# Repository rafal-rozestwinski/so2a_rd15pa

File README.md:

# so2a_rd15pa

Go to the [FULL BOARD](v1/so2a_rd15_pa_v1/) or [MINIMAL BOARD](v1/so2a_rd15_pa_v1-minimal/)

## Images

## Join HamBrewers on Telegram:

http://t.me/hambrewers

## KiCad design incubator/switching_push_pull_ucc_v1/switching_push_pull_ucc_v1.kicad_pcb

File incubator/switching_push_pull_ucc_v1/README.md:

# switching_push_pull_amp

## Join HamBrewers on Telegram:

http://t.me/hambrewers

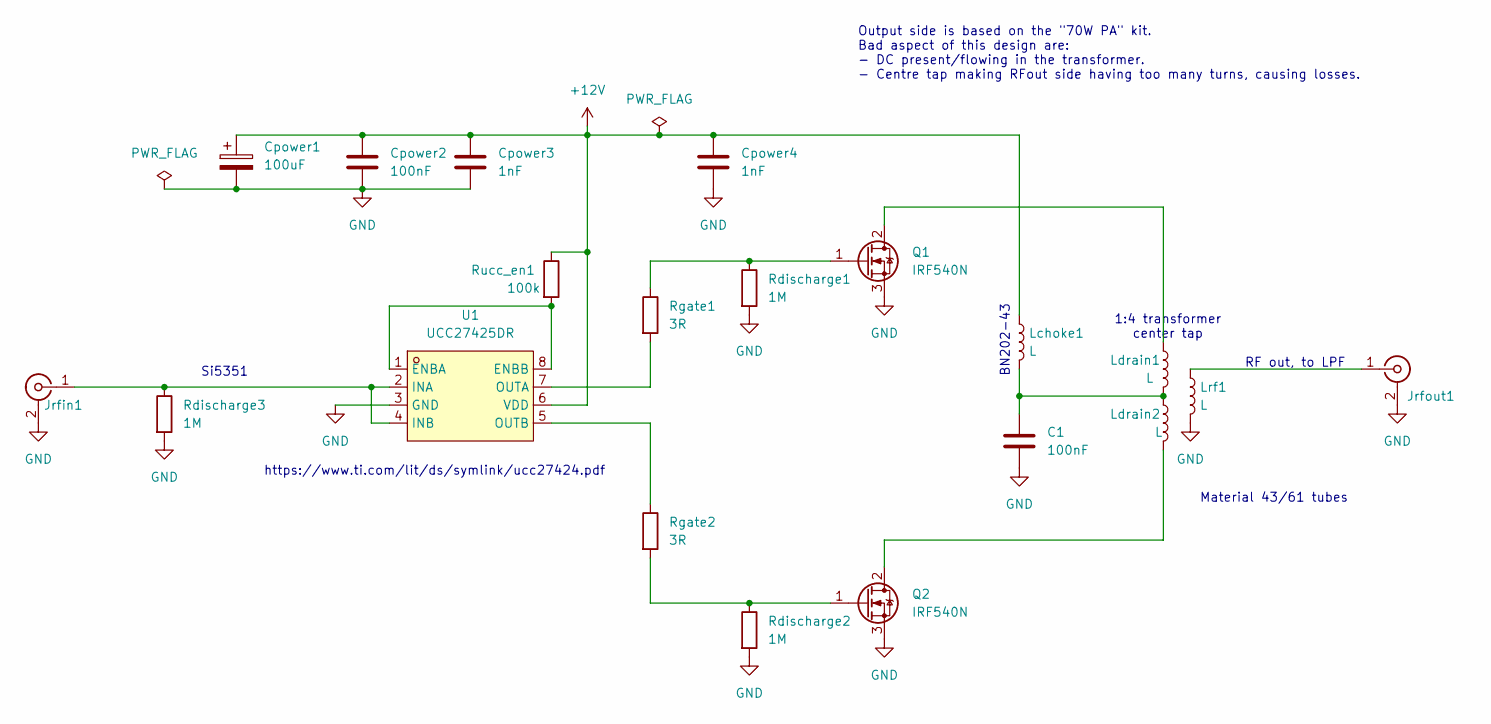
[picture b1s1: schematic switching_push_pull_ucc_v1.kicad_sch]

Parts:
C1: 100nF; C_1206_3216Metric
Cpower1: 100uF; C_Elec_8x10.2
Cpower2: 100nF; C_1206_3216Metric
Cpower3, Cpower4: 1nF; C_1206_3216Metric
Jrfin1: Conn_Coaxial; SMA_EDGELAUNCH_Modded
Jrfout1: Conn_Coaxial; SMA_EDGELAUNCH_Modded
Lchoke1: L; L_Wuerth_HCM-1050
Ldrain1, Ldrain2: L; L_Wuerth_HCM-1050
Lrf1: L; L_Wuerth_HCM-1050
Q1, Q2: IRF540N; TO-220-3_Vertical
Rdischarge1, Rdischarge2, Rdischarge3: 1M; R_0805_2012Metric
Rgate1, Rgate2: 3R; R_2010_5025Metric
Rucc_en1: 100k; R_0805_2012Metric
U1: UCC27425DR; SOIC-8_L4.9-W3.9-P1.27-LS6.0-BL; LCSC Part C1848352

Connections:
+12V: Cpower1.1, Cpower2.1, Cpower3.1, Cpower4.1, Lchoke1.1, Rucc_en1.1, U1.6 (VDD); also elsewhere on the board
GND: C1.2, Cpower1.2, Cpower2.2, Cpower3.2, Cpower4.2, Jrfin1.2 (Ext), Jrfout1.2 (Ext), Lrf1.2, Q1.3 (S), Q2.3 (S), Rdischarge1.2, Rdischarge2.2, Rdischarge3.2, U1.3 (GND)
unnamed: C1.1, Lchoke1.2, Ldrain1.2, Ldrain2.1
unnamed: Jrfin1.1 (In), Rdischarge3.1, U1.2 (INA), U1.4 (INB)
unnamed: Jrfout1.1 (In), Lrf1.1
unnamed: Ldrain1.1, Q1.2 (D)
unnamed: Q1.1 (G), Rdischarge1.1, Rgate1.1
unnamed: Ldrain2.2, Q2.2 (D)
unnamed: Q2.1 (G), Rdischarge2.1, Rgate2.2
unnamed: Rucc_en1.2, U1.1 (ENBA), U1.8 (ENBB)
unnamed: Rgate1.2, U1.7 (OUTA)
unnamed: Rgate2.1, U1.5 (OUTB)

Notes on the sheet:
1:4 transformer center tap
BN202-43
Material 43/61 tubes
https://www.ti.com/lit/ds/symlink/ucc27424.pdf
Output side is based on the "70W PA" kit. Bad aspect of this design are: - DC present/flowing in the transformer. - Centre tap making RFout side having too many turns, causing losses.
Si5351
RF out, to LPF

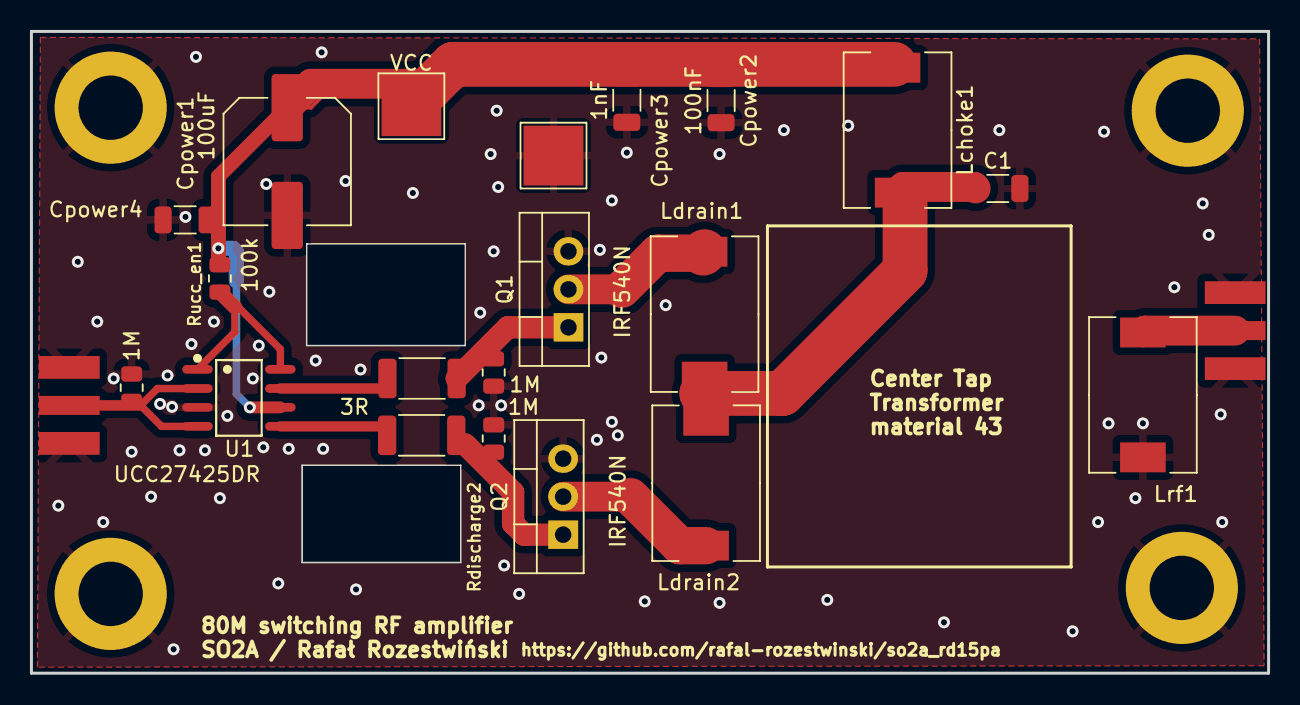
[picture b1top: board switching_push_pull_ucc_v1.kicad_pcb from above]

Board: 2 copper layers, 82.7 x 42.9 mm, 21 parts (0 on the bottom side), 12 nets.

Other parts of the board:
VCC: TestPoint_Pad_4.0x4.0mm

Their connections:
+12V: VCC.1; also elsewhere on the board

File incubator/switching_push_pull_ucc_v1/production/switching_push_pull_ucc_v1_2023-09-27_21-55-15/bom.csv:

Designator,Footprint,Quantity,Value,LCSC Part #
"C1, Cpower2",1206,2,100nF,
Cpower1,C_Elec_8x10.2,1,100uF,
"Cpower3, Cpower4",1206,2,1nF,
"Jrfin1, Jrfout1",SMA_EDGELAUNCH_Modded,2,Conn_Coaxial,
"Lchoke1, Ldrain1, Ldrain2, Lrf1",L_Wuerth_HCM-1050,4,L,
"Q1, Q2",TO-220-3_Vertical,2,IRF540N,
"Rdischarge1, Rdischarge2, Rdischarge3",0805,3,1M,
"Rgate1, Rgate2",2010,2,3R,
Rucc_en1,0805,1,100k,
U1,SOIC-8_L4.9-W3.9-P1.27-LS6.0-BL,1,UCC27425DR,C1848352

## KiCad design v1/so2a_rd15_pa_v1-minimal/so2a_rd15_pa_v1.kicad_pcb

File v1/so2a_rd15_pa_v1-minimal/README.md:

# so2a_rd15pa - MINIMAL

## Join HamBrewers on Telegram:

http://t.me/hambrewers

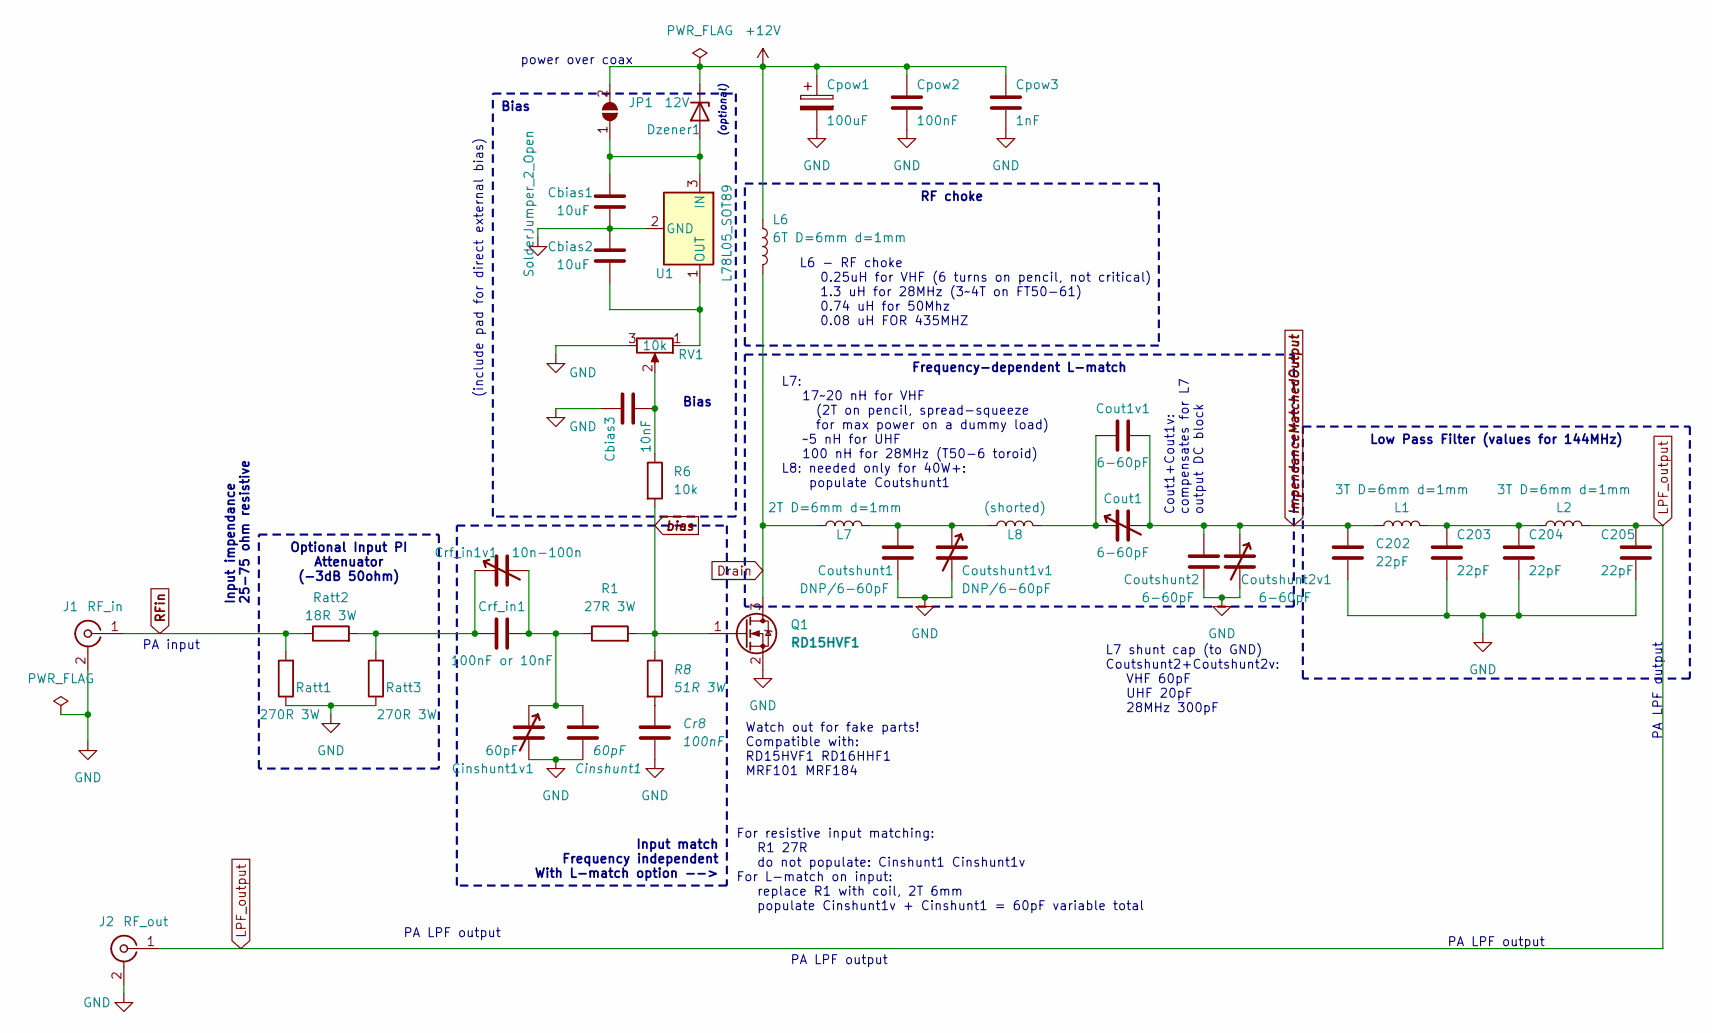
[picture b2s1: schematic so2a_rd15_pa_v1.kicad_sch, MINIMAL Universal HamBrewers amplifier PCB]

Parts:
C202, C203, C204, C205: 22pF; C_1206_3216Metric
Cbias1, Cbias2: 10uF; C_1206_3216Metric
Cbias3: 10nF; C_1206_3216Metric
Cinshunt1: 60pF; C_1206_3216Metric
Cinshunt1v1: 60pF; C_Trimmer_Murata_TZB4-B
Cout1: 6-60pF; C_Trimmer_Murata_TZB4-B
Cout1v1: 6-60pF; C_1206_3216Metric
Coutshunt1: DNP/6-60pF; C_1206_3216Metric
Coutshunt1v1: DNP/6-60pF; C_Trimmer_Murata_TZB4-B
Coutshunt2: 6-60pF; C_1206_3216Metric
Coutshunt2v1: 6-60pF; C_Trimmer_Murata_TZB4-B
Cpow1: 100uF; C_Elec_8x10.2
Cpow2: 100nF; C_1206_3216Metric
Cpow3: 1nF; C_1206_3216Metric
Cr8: 100nF; C_1206_3216Metric
Crf_in1: 100nF or 10nF; C_1206_3216Metric
Crf_in1v1: 10n-100n; C_Trimmer_Murata_TZB4-B
Dzener1: 12V; D_SOD-123
J1: RF_in; SMA_EDGELAUNCH_Modded
J2: RF_out; SMA_EDGELAUNCH_Modded
JP1: SolderJumper_2_Open; SolderJumper-2_P1.3mm_Open_TrianglePad1.0x1.5mm
L1, L2: 3T D=6mm d=1mm; L_Wuerth_HCM-1050
L6: 6T D=6mm d=1mm; L_Wuerth_HCM-1050
L7: 2T D=6mm d=1mm; L_Wuerth_HCM-1050
L8: (shorted); L_Wuerth_HCM-1050
Q1: RD15HVF1; SO2A_TO-220F-3_Vertical_SMD
R1: 27R 3W; R_2010_5025Metric
R6: 10k; R_0805_2012Metric
R8: 51R 3W; R_2010_5025Metric
RV1: 10k; Potentiometer_Vishay_TS53YL_Vertical
Ratt1, Ratt3: 270R 3W; R_2010_5025Metric
Ratt2: 18R 3W; R_2010_5025Metric
U1: L78L05_SOT89; SOT-89-3

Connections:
+12V: Cpow1.1, Cpow2.1, Cpow3.1, Dzener1.1 (K), JP1.2 (B), L6.1; also elsewhere on the board
Drain: L6.2, L7.1, Q1.3 (D)
GND: C202.1, C203.1, C204.1, C205.1, Cbias1.2, Cbias2.1, Cbias3.1, Cinshunt1.1, Cinshunt1v1.2, Coutshunt1.1, Coutshunt1v1.2, Coutshunt2.1, Coutshunt2v1.2, Cpow1.2, Cpow2.2, Cpow3.2, Cr8.1, J1.2 (Ext), J2.2 (Ext), Q1.2 (S), RV1.3, Ratt1.1, Ratt3.1, U1.2 (GND); also elsewhere on the board
ImpendanceMatchedOutput: C202.2, Cout1.2, Cout1v1.1, Coutshunt2.2, Coutshunt2v1.1, L1.1
LPF_output: C205.2, J2.1 (In), L2.2
unnamed: C203.2, C204.2, L1.2, L2.1
unnamed: Cbias3.2, R6.1, RV1.2
unnamed: Cinshunt1.2, Cinshunt1v1.1, Crf_in1.2, Crf_in1v1.2, R1.1
unnamed: Cout1.1, Cout1v1.2, L8.2
unnamed: Coutshunt1.2, Coutshunt1v1.1, L7.2, L8.1
unnamed: Cr8.2, R8.2
unnamed: Crf_in1.1, Crf_in1v1.1, Ratt2.2, Ratt3.2
unnamed: Cbias1.1, Dzener1.2 (A), JP1.1 (A), U1.3 (IN)
unnamed: Cbias2.2, RV1.1, U1.1 (OUT)
RFin: J1.1 (In), Ratt1.2, Ratt2.1
bias: Q1.1 (G), R1.2, R6.2, R8.1

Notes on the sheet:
Frequency-dependent L-match
Bias
Low Pass Filter (values for 144MHz)
Input match Frequency independent With L-match option -->
Optional Input PI Attenuator (-3dB 50ohm)
RF choke
Watch out for fake parts! Compatible with: RD15HVF1 RD16HHF1 MRF101 MRF184
Input impendance 25-75 ohm resistive
PA LPF output
For resistive input matching: R1 27R do not populate: Cinshunt1 Cinshunt1v For L-match on input: replace R1 with coil, 2T 6mm populate Cinshunt1v + Cinshunt1 = 60pF variable total
PA input
L6 - RF choke 0.25uH for VHF (6 turns on pencil, not critical) 1.3 uH for 28MHz (3~4T on FT50-61) 0.74 uH for 50Mhz 0.08 uH FOR 435MHZ
(include pad for direct external bias)
Cout1+Cout1v: compensates for L7 output DC block
power over coax
L7 shunt cap (to GND) Coutshunt2+Coutshunt2v: VHF 60pF UHF 20pF 28MHz 300pF
(optional)
L7: 17~20 nH for VHF (2T on pencil, spread-squeeze for max power on a dummy load) ~5 nH for UHF 100 nH for 28MHz (T50-6 toroid) L8: needed only for 40W+: populate Coutshunt1

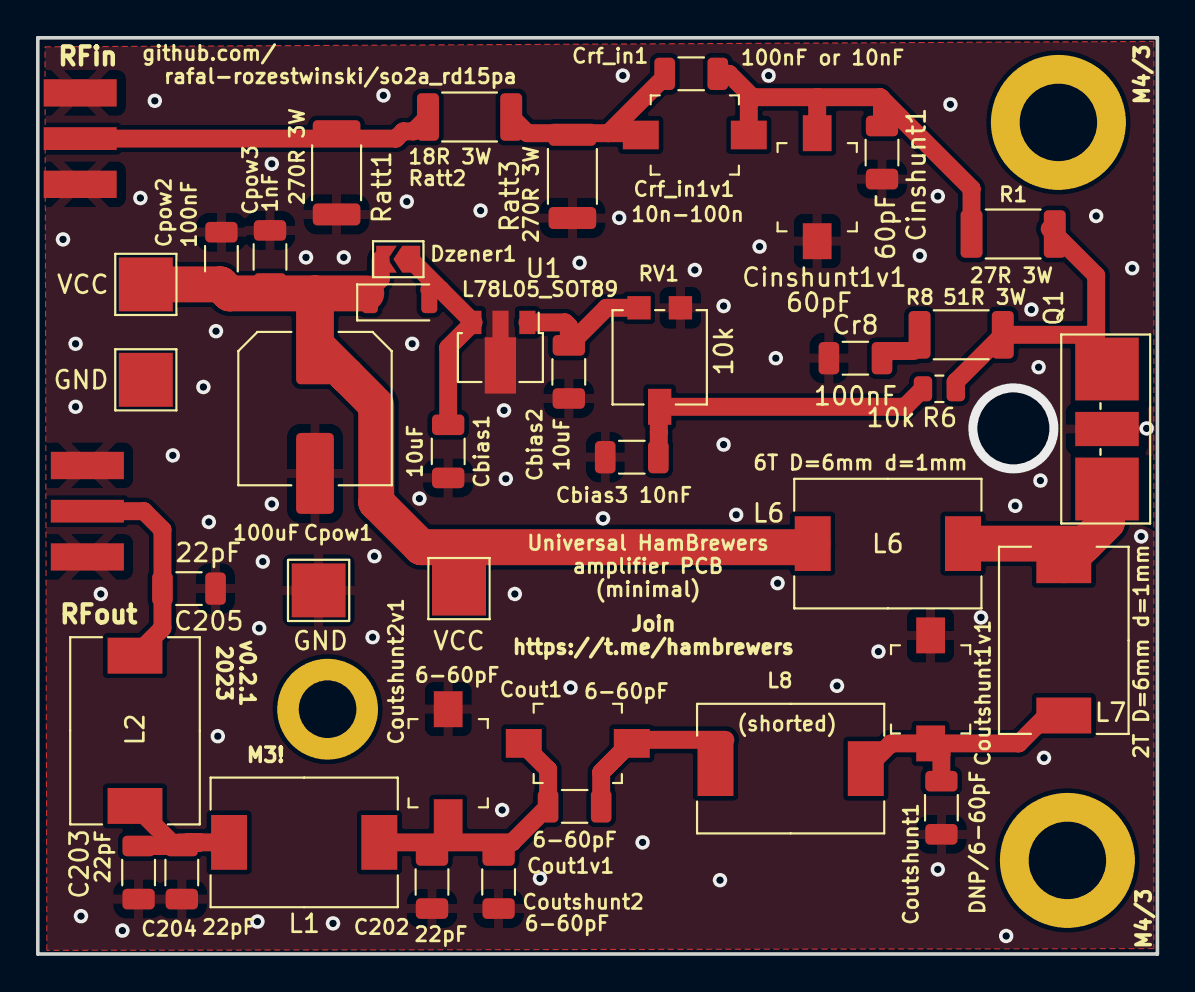
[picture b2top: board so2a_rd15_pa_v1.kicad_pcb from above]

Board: 2 copper layers, 62.2 x 50.9 mm, 43 parts (0 on the bottom side), 16 nets.

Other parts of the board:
GND: TestPoint_Pad_3.0x3.0mm
GND#2: TestPoint_Pad_3.0x3.0mm
VCC: TestPoint_Pad_3.0x3.0mm
VCC#2: TestPoint_Pad_3.0x3.0mm

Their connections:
+12V: VCC.1, VCC#2.1; also elsewhere on the board
GND: GND.1; also elsewhere on the board

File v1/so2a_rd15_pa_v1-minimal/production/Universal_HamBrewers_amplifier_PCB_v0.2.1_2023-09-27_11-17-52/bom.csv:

Designator,Footprint,Quantity,Value,LCSC Part #
"C202, C203, C204, C205",1206,4,22pF,
"Cbias1, Cbias2",1206,2,10uF,
Cbias3,1206,1,10nF,
Cinshunt1,1206,1,60pF,
Cinshunt1v1,C_Trimmer_Murata_TZB4-B,1,60pF,
"Cout1, Coutshunt2v1",C_Trimmer_Murata_TZB4-B,2,6-60pF,
"Cout1v1, Coutshunt2",1206,2,6-60pF,
Coutshunt1,1206,1,DNP/6-60pF,
Coutshunt1v1,C_Trimmer_Murata_TZB4-B,1,DNP/6-60pF,
Cpow1,C_Elec_8x10.2,1,100uF,
"Cpow2, Cr8",1206,2,100nF,
Cpow3,1206,1,1nF,
Crf_in1,1206,1,100nF or 10nF,
Crf_in1v1,C_Trimmer_Murata_TZB4-B,1,10n-100n,
Dzener1,D_SOD-123,1,12V,
J1,SMA_EDGELAUNCH_Modded,1,RF_in,
J2,SMA_EDGELAUNCH_Modded,1,RF_out,
JP1,SolderJumper-2_P1.3mm_Open_TrianglePad1.0x1.5mm,1,SolderJumper_2_Open,
"L1, L2",L_Wuerth_HCM-1050,2,3T D=6mm d=1mm,
L6,L_Wuerth_HCM-1050,1,6T D=6mm d=1mm,
L7,L_Wuerth_HCM-1050,1,2T D=6mm d=1mm,
L8,L_Wuerth_HCM-1050,1,(shorted),
Q1,SO2A_TO-220F-3_Vertical_SMD,1,RD15HVF1,
R1,2010,1,27R 3W,
R6,0805,1,10k,
R8,2010,1,51R 3W,
RV1,Potentiometer_Vishay_TS53YL_Vertical,1,10k,
"Ratt1, Ratt3",2010,2,270R 3W,
Ratt2,2010,1,18R 3W,
U1,SOT-89-3,1,L78L05_SOT89,

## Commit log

2023-09-26 v0.2.1
2023-09-27 v0.3.1: Adding minimal board; changes for the drain trace width
2023-09-27 incubator - switching push pull ucc for 80m
2023-09-27 incubator-schematic
2023-09-28 cleanup
